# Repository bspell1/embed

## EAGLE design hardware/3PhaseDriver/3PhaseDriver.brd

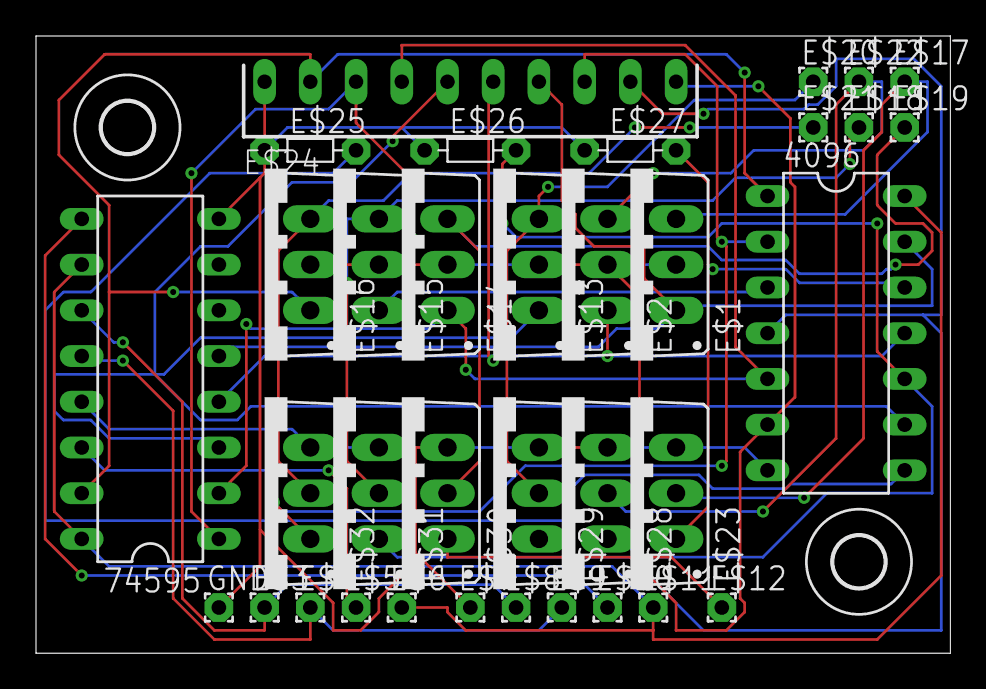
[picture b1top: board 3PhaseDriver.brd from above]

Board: 2 copper layers, 50.8 x 34.3 mm, 37 parts (0 on the bottom side), 25 nets.

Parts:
4096: 4069; DIL14
74595: 74595; DIL16
E$1, E$2, E$13, E$14, E$15, E$16, E$23, E$28, E$29, E$30, E$31, E$32: TO220V
E$3, E$4, E$5, E$6, E$7, E$8, E$9, E$10, E$11, E$12, E$17, E$18, E$19, E$20, E$21, E$22: 1,6/0,8
E$24: SIP-10
E$25, E$26, E$27: R-5
E$40, E$42: 2,8
GND: 1,6/0,8

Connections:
S$1: 4096.7, 74595.8, 74595.13, E$7.1, E$23.3, E$24.1, E$25.1, E$26.1, E$27.1, E$28.3, E$29.3, E$30.3, E$31.3, E$32.3, GND.1
S$2: 4096.14, 74595.10, 74595.16, E$6.1, E$11.1
S$3: 74595.11, E$3.1, E$8.1
S$4: 74595.12, E$4.1, E$9.1
S$5: 74595.14, E$5.1
S$6: 74595.9, E$10.1
S$7: 4096.1, 74595.15, E$16.1, E$24.2
S$8: 4096.3, 74595.1, E$15.1, E$24.3
S$9: E$1.2, E$2.2, E$12.1, E$13.2, E$14.2, E$15.2, E$16.2
S$11: 4096.5, 74595.2, E$14.1, E$24.4
S$15: 4096.9, 74595.3, E$13.1, E$24.5
S$16: 4096.11, 74595.4, E$2.1, E$24.6
S$17: 4096.13, 74595.5, E$1.1, E$24.7
S$18: 4096.2, E$24.8, E$32.1
S$19: 4096.4, E$24.9, E$31.1
S$20: 4096.6, E$24.10, E$30.1
S$25: 4096.8, E$25.2, E$29.1
S$26: 4096.10, E$26.2, E$28.1
S$27: 4096.12, E$23.1, E$27.2
S$28: E$16.3, E$21.1, E$32.2
S$29: E$15.3, E$18.1, E$31.2
S$30: E$14.3, E$19.1, E$30.2
S$31: E$13.3, E$20.1, E$29.2
S$32: E$2.3, E$22.1, E$28.2
S$33: E$1.3, E$17.1, E$23.2

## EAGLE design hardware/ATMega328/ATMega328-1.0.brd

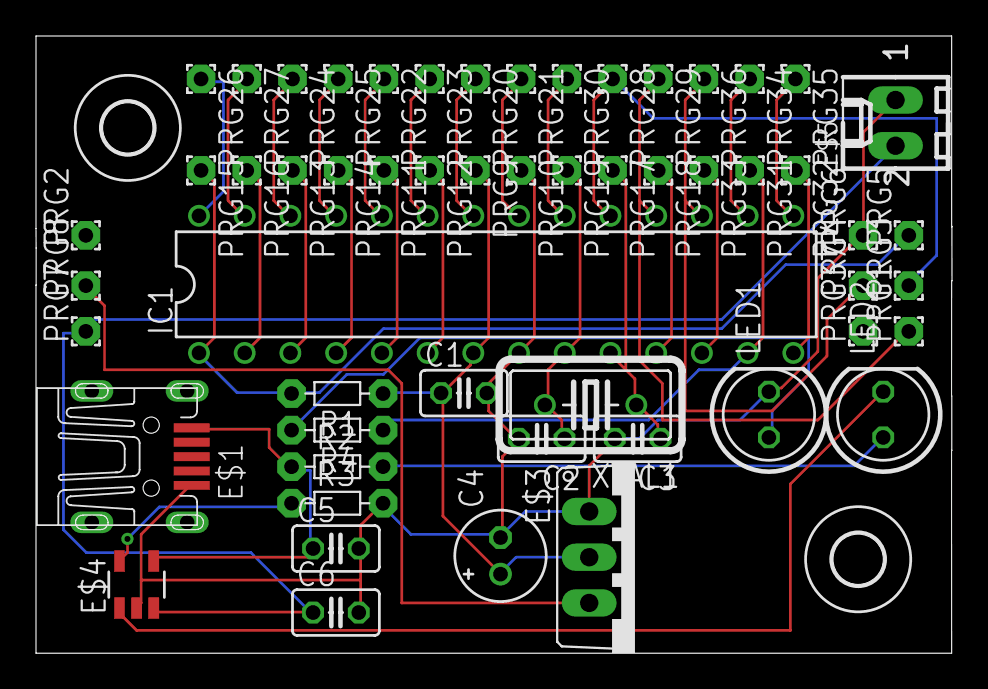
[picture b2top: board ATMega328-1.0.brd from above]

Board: 2 copper layers, 50.9 x 34.3 mm, 57 parts (0 on the bottom side), 35 nets.

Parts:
C1, C2, C3, C5, C6: C025-025X050
C4: E2-5
E$1: UX60-MB-5S8
E$2, E$14: 2,8
E$3: TO220V
E$4: SOT23-5
E$5: 6410-02
IC1: PDIP-T28
LED1, LED2: LED5MM
PRG1, PRG2, PRG3, PRG4, PRG5, PRG6, PRG7, PRG8, PRG9, PRG10, PRG11, PRG12, PRG13, PRG14, PRG15, PRG16, PRG17, PRG18, PRG19, PRG20, PRG21, PRG22, PRG23, PRG24, PRG25, PRG26, PRG27, PRG28, PRG29, PRG30, PRG31, PRG32, PRG33, PRG34, PRG35, PRG36, PRG37: 1,6/0,8
R1, R2, R3, R4: R-5
XTAL1: HC18U-V

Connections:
S$2: C1.2, C2.2, C3.2, C4.-, C5.2, C6.2, E$1.5, E$3.1, E$4.2, E$5.1, IC1.8, LED1.K, PRG6.1, PRG10.1, R3.2
S$3: E$4.1, LED2.K
S$4: IC1.26, PRG24.1
S$5: IC1.13, PRG31.1, R4.1
S$6: C2.1, IC1.9, PRG19.1, XTAL1.2
S$7: C3.1, IC1.10, PRG17.1, XTAL1.1
S$8: IC1.1, PRG5.1, PRG15.1, R1.2
S$9: IC1.18, PRG1.1, PRG29.1
S$10: C1.1, C4.+, E$3.2, IC1.7, PRG9.1, R1.1
S$11: IC1.15, PRG35.1
S$12: IC1.19, PRG3.1, PRG28.1
S$13: IC1.17, PRG4.1, PRG36.1
S$14: IC1.14, PRG32.1
S$15: IC1.16, PRG34.1
S$16: IC1.4, PRG14.1
S$17: IC1.28, PRG26.1
S$18: IC1.5, PRG11.1
S$19: IC1.27, PRG27.1
S$20: E$3.3, PRG8.1
S$21: IC1.2, PRG16.1
S$22: LED1.A, R4.2
S$23: IC1.3, PRG13.1
S$24: IC1.6, PRG12.1
S$25: IC1.11, PRG18.1
S$26: IC1.12, PRG33.1
S$27: IC1.25, PRG25.1
S$28: IC1.24, PRG22.1
S$29: IC1.23, PRG23.1
S$30: IC1.22, PRG20.1
S$31: IC1.21, PRG21.1
S$32: IC1.20, PRG30.1
S$33: LED2.A, R2.2
S$34: C6.1, E$4.3, E$5.2, PRG7.1
S$35: C5.1, E$1.1, E$4.4, R2.1
S$36: E$4.5, R3.1

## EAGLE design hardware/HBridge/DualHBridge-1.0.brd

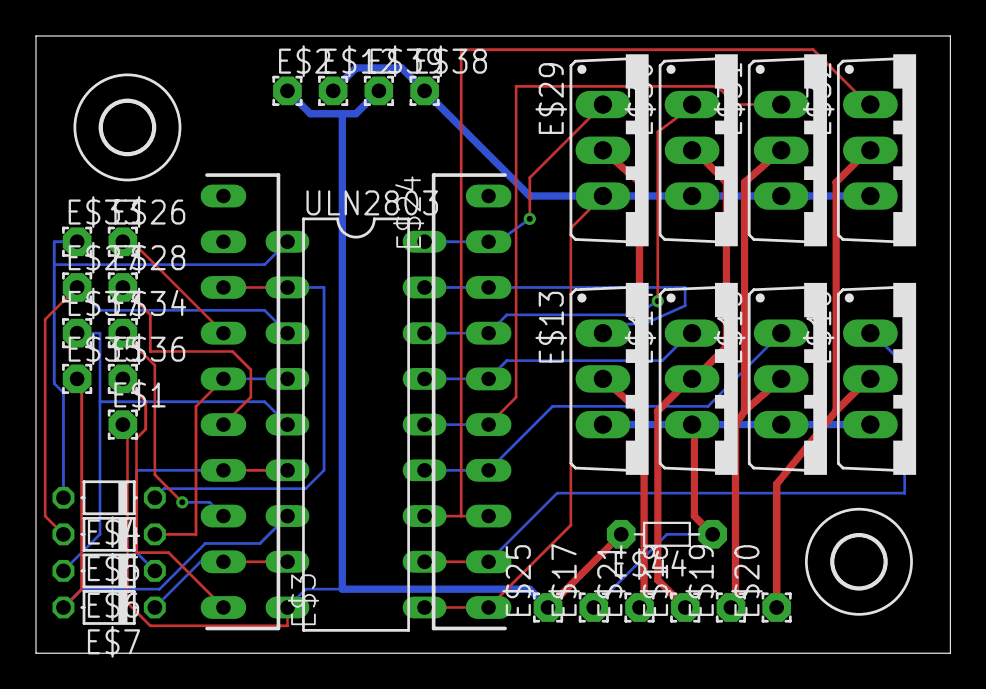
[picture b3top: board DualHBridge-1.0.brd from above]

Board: 2 copper layers, 50.8 x 34.3 mm, 37 parts (0 on the bottom side), 27 nets.

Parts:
E$1, E$2, E$12, E$17, E$18, E$19, E$20, E$21, E$25, E$26, E$27, E$28, E$33, E$34, E$35, E$36, E$37, E$38, E$39: 1,6/0,8
E$3, E$24: SIP-10
E$4, E$5, E$6, E$7: D-5
E$13, E$14, E$15, E$16, E$29, E$30, E$31, E$32: TO220V
E$40, E$42: 2,8
E$44: R-5
ULN2803: ULN2803; DIL18

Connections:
S$1: E$12.1, E$24.10, E$29.3, E$30.3, E$31.3, E$32.3, E$38.1, ULN2803.10
S$2: E$3.7, E$26.1
S$3: E$3.8, E$4.C, ULN2803.2
S$4: E$3.6, E$5.C, ULN2803.4
S$5: E$3.4, E$6.C, ULN2803.6
S$6: E$24.2, E$29.1, ULN2803.18
S$7: E$24.6, E$31.1, ULN2803.14
S$8: E$13.1, E$24.3, ULN2803.17
S$9: E$24.4, E$30.1, ULN2803.16
S$10: E$14.1, E$24.5, ULN2803.15
S$11: E$4.A, E$33.1, ULN2803.1
S$12: E$1.1, E$2.1, E$25.1, E$39.1, E$44.2, ULN2803.9
S$13: E$15.1, E$24.7, ULN2803.13
S$14: E$24.8, E$32.1, ULN2803.12
S$15: E$16.1, E$24.9, ULN2803.11
S$16: E$3.5, E$28.1
S$17: E$5.A, E$27.1, ULN2803.3
S$18: E$3.3, E$34.1
S$19: E$6.A, E$37.1, ULN2803.5
S$20: E$3.1, E$36.1
S$21: E$7.A, E$35.1, ULN2803.7
S$22: E$3.2, E$7.C, ULN2803.8
S$24: E$13.3, E$14.3, E$15.3, E$16.3, E$17.1, E$44.1
S$25: E$13.2, E$21.1, E$29.2
S$26: E$14.2, E$18.1, E$30.2
S$27: E$15.2, E$19.1, E$31.2
S$28: E$16.2, E$20.1, E$32.2

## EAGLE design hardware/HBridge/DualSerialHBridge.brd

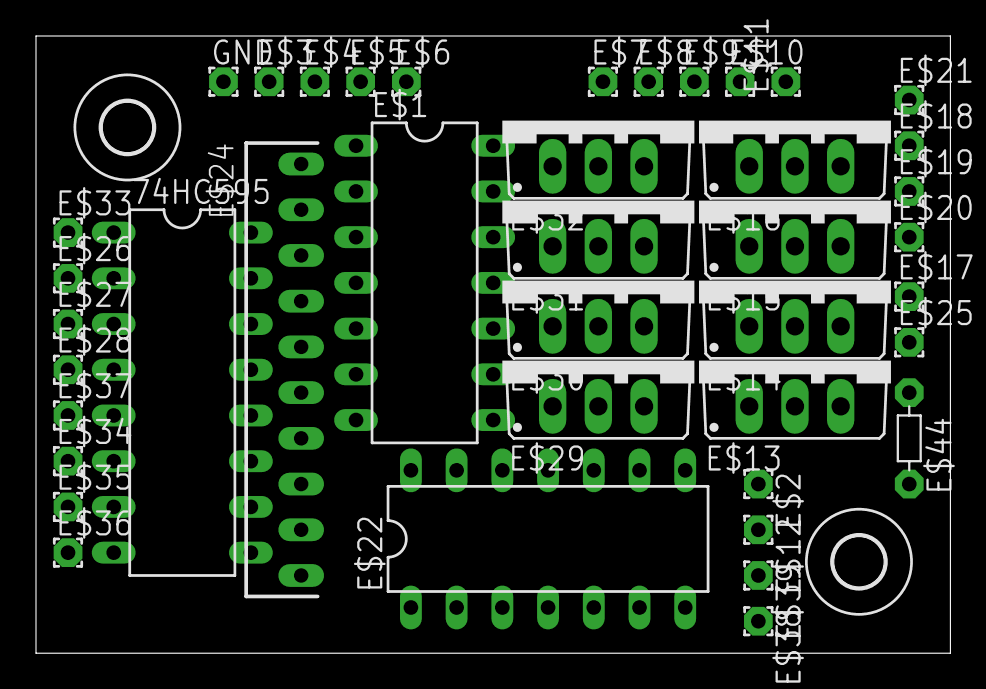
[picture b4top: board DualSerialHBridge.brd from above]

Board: 2 copper layers, 50.8 x 34.3 mm, 43 parts (0 on the bottom side), 28 nets, no tracks yet.

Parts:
74HC595: 74HC595; DIL16
E$1, E$22: LM324; DIL14
E$2, E$3, E$4, E$5, E$6, E$7, E$8, E$9, E$10, E$11, E$12, E$17, E$18, E$19, E$20, E$21, E$25, E$26, E$27, E$28, E$33, E$34, E$35, E$36, E$37, E$38, E$39: 1,6/0,8
E$13, E$14, E$15, E$16, E$29, E$30, E$31, E$32: TO220V
E$24: SIP-10
E$40, E$42: 2,8
E$44: R-5
GND: 1,6/0,8

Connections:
S$1: E$1.1, E$32.1
S$2: 74HC595.10, 74HC595.16, E$6.1, E$11.1
S$3: 74HC595.11, E$3.1, E$8.1
S$4: 74HC595.12, E$4.1, E$9.1
S$5: 74HC595.14, E$5.1
S$6: E$1.4, E$12.1, E$22.4, E$29.2, E$30.2, E$31.2, E$32.2, E$38.1
S$7: E$1.7, E$16.1
S$8: E$1.8, E$31.1
S$9: E$1.14, E$15.1
S$10: E$22.1, E$30.1
S$11: 74HC595.15, E$1.3, E$1.6, E$24.9, E$33.1
S$12: 74HC595.8, 74HC595.13, E$1.11, E$2.1, E$7.1, E$22.11, E$24.10, E$25.1, E$39.1, E$44.2, GND.1
S$13: E$14.1, E$22.7
S$14: E$22.8, E$29.1
S$15: E$13.1, E$22.14
S$16: 74HC595.1, E$1.2, E$1.5, E$24.8, E$26.1
S$17: 74HC595.2, E$1.10, E$1.13, E$24.7, E$27.1
S$18: 74HC595.3, E$1.9, E$1.12, E$24.6, E$28.1
S$19: 74HC595.4, E$22.3, E$22.6, E$24.5, E$37.1
S$20: 74HC595.5, E$22.2, E$22.5, E$24.4, E$34.1
S$21: 74HC595.6, E$22.10, E$22.13, E$24.3, E$35.1
S$22: 74HC595.9, E$10.1
S$23: 74HC595.7, E$22.9, E$22.12, E$24.2, E$36.1
S$24: E$13.3, E$14.3, E$15.3, E$16.3, E$17.1, E$44.1
S$25: E$16.2, E$21.1, E$32.3
S$26: E$15.2, E$18.1, E$31.3
S$27: E$14.2, E$19.1, E$30.3
S$28: E$13.2, E$20.1, E$29.3

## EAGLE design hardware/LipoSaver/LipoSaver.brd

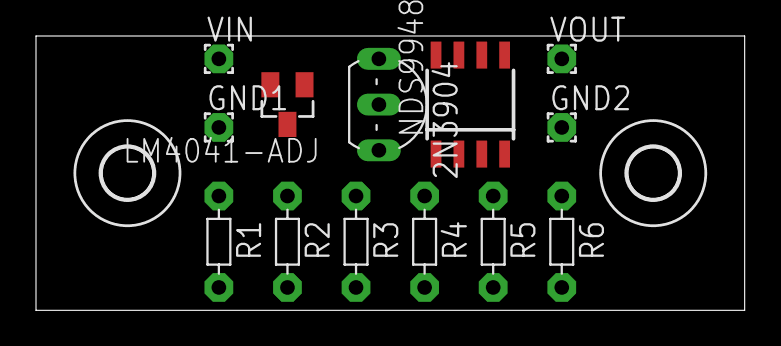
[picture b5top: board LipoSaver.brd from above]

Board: 2 copper layers, 39.4 x 15.2 mm, 15 parts (0 on the bottom side), 7 nets, no tracks yet.

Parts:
2N3904: TO92-EBC
E$40, E$42: 2,8
GND1, GND2: 1,6/0,8
LM4041-ADJ: SOT23
NDS9948: SOIC8
R1: R1; R-5
R2: R2; R-5
R3: 10K; R-5
R4: 4.7M; R-5
R5: 100K; R-5
R6: 20K; R-5
VIN: 1,6/0,8
VOUT: 1,6/0,8

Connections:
S$1: 2N3904.E, GND1.1, GND2.1, NDS9948.3, NDS9948.4, NDS9948.5, NDS9948.6, NDS9948.7, R2.2, R3.2
S$2: LM4041-ADJ.2, NDS9948.1, R1.1, R6.1, VIN.1
S$3: LM4041-ADJ.3, R3.1, R5.2
S$4: 2N3904.C, NDS9948.2, R4.1, R6.2
S$5: 2N3904.B, R5.1
S$6: NDS9948.8, VOUT.1
S$11: LM4041-ADJ.1, R1.2, R2.1, R4.2
